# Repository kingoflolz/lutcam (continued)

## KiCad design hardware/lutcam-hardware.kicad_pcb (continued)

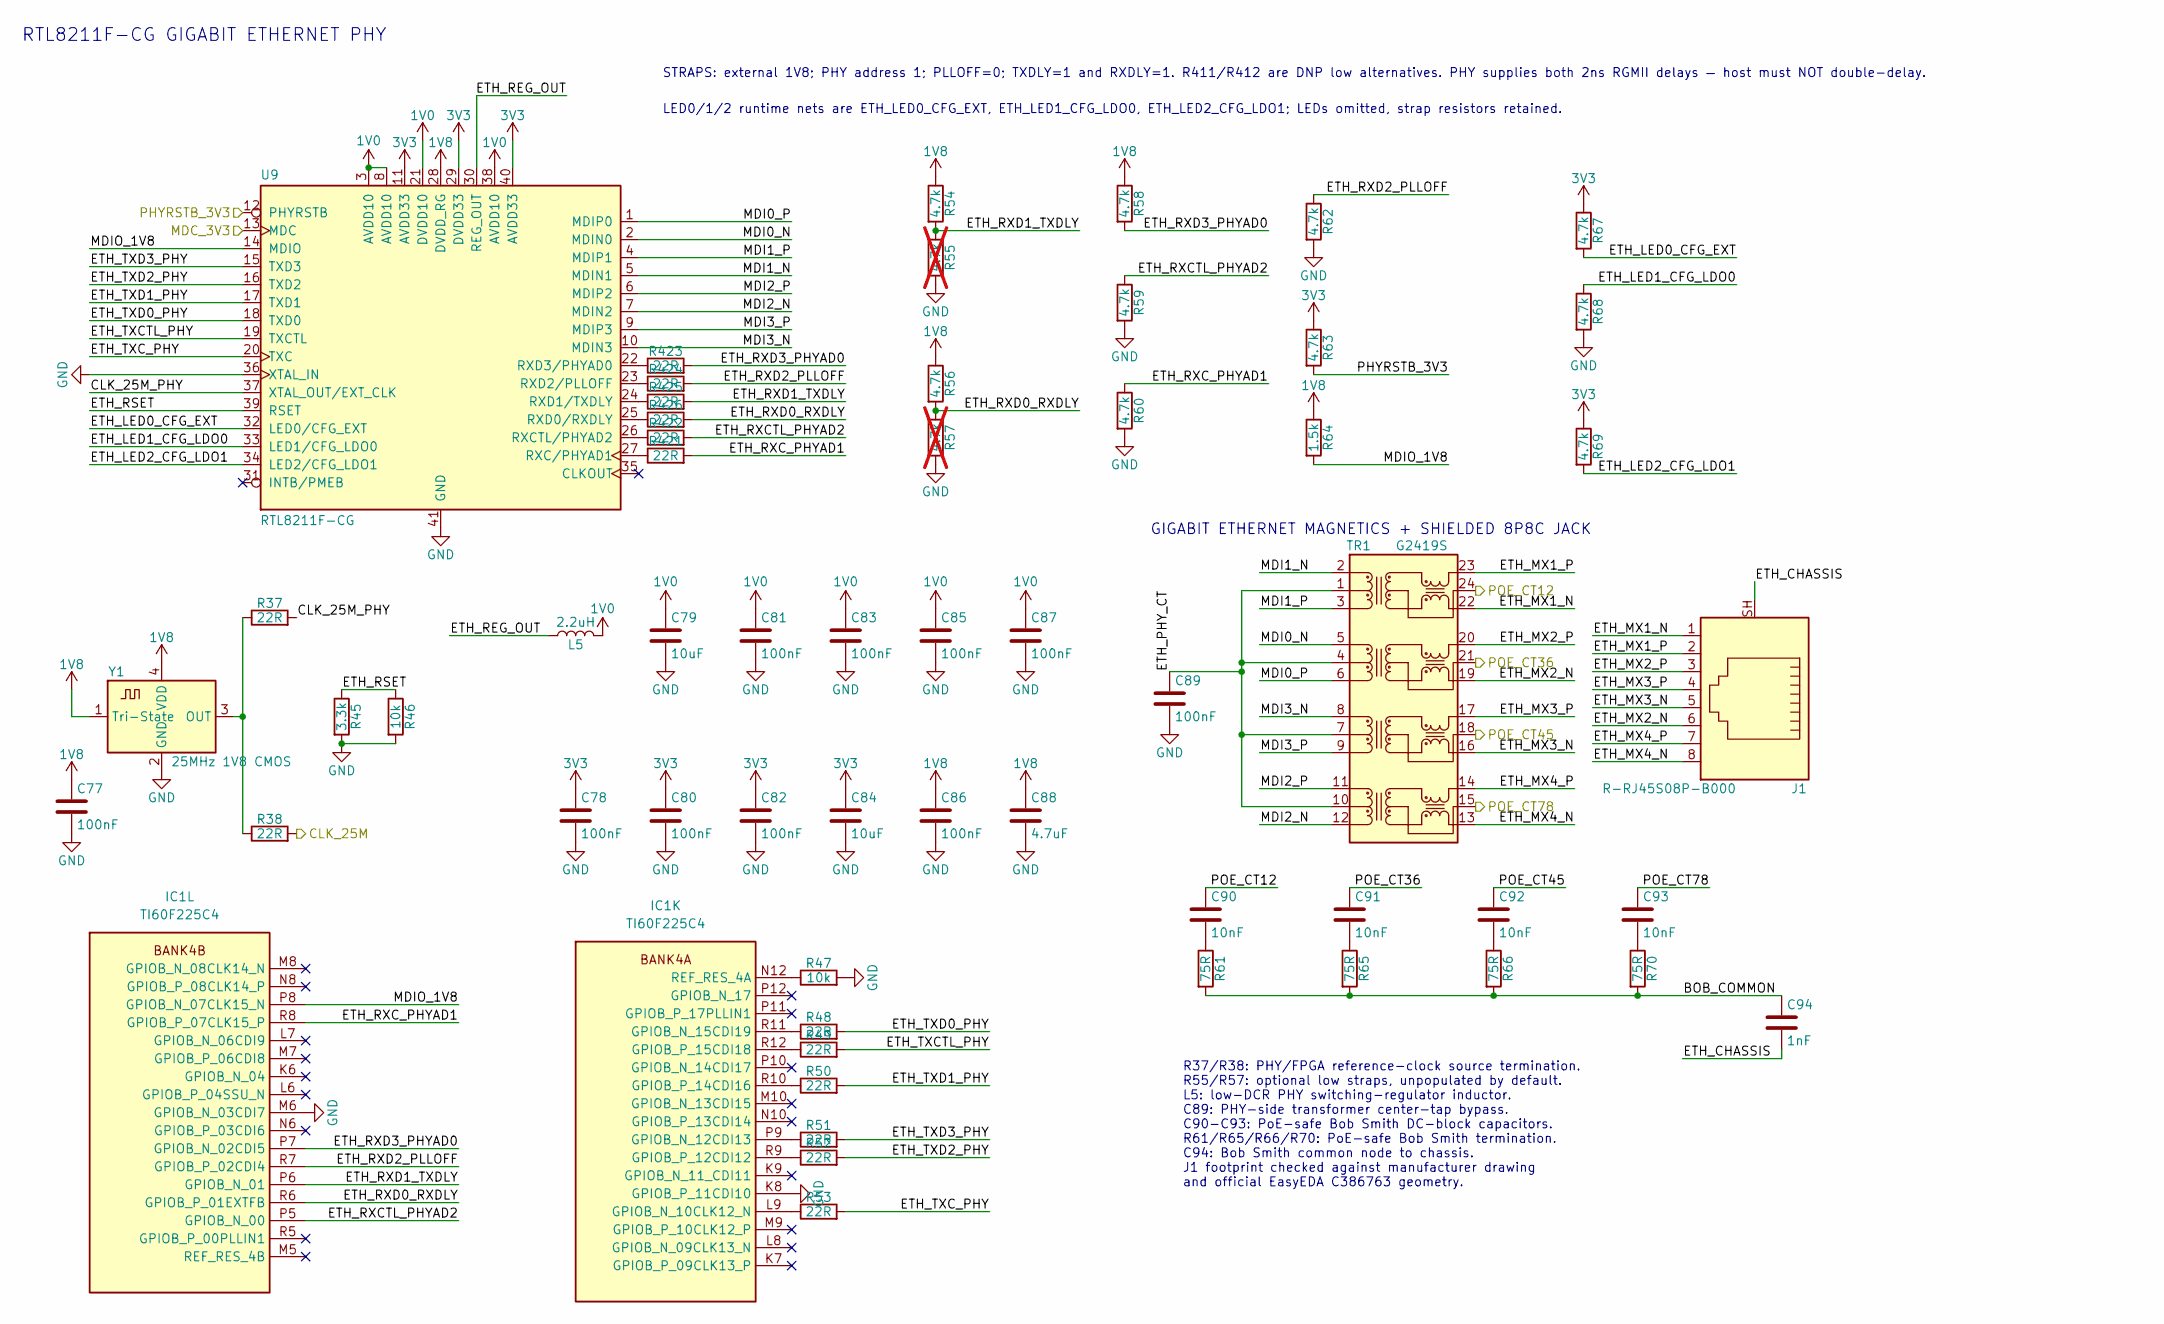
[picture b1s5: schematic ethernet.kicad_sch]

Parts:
C77, C78, C80, C81, C82, C83, C85, C86, C87: 100nF; C_0402_1005Metric; MPN CL05B104KO5NNNC; JLCPCB Library Basic
C79, C84: 10uF; C_0603_1608Metric; MPN CL10A106KP8NNNC; JLCPCB Library Basic
C88: 4.7uF; C_0603_1608Metric; MPN CL10A475KO8NNNC; JLCPCB Library Basic
C89: 100nF; C_0402_1005Metric; MPN CL05B104KO5NNNC; LCSC C1525
C90, C91, C92, C93: 10nF; C_0402_1005Metric; MPN CC0402KRX7R0BB103; LCSC C527014
C94: 1nF; C_1206_3216Metric; MPN 1206B102K202NT; LCSC C9196
IC1: TI60F225C4; BGA225C65P15X15_1000X1000X100; Manufacturer_Part_Number TI60F225C4
J1: R-RJ45S08P-B000; R-RJ45S08P-B000_8P8C_Vertical; MPN R-RJ45S08P-B000; LCSC C386763
L5: 2.2uH; L_Changjiang_FTC252012S; MPN FTC252012S2R2MBCA; JLCPCB Library Extended
R37, R38: 22R; R_0402_1005Metric; MPN 0402WGF220JTCE; LCSC C25092
R45: 3.3k; R_0402_1005Metric; MPN 0402WGF3301TCE; JLCPCB Library Basic
R46, R47: 10k; R_0402_1005Metric; MPN 0402WGF1002TCE; JLCPCB Library Basic
R48, R49, R50, R51, R52, R53, R421, R422, R423, R424, R425, R426: 22R; R_0402_1005Metric; MPN 0402WGF220JTCE; JLCPCB Library Basic
R54, R56, R58, R59, R60, R62, R63, R67, R68, R69: 4.7k; R_0402_1005Metric; MPN 0402WGF4701TCE; JLCPCB Library Basic
R55, R57: 4.7k; R_0402_1005Metric; MPN 0402WGF4701TCE; JLCPCB Library Basic; not fitted
R61, R65, R66, R70: 75R; R_0402_1005Metric; MPN 0402WGF750JTCE; LCSC C25133
R64: 1.5k; R_0402_1005Metric; MPN 0402WGF1501TCE; JLCPCB Library Basic
TR1: G2419S; G2419S_Transformer_SMD-24_15.1x7.1mm_P1.0mm; MPN G2419S; LCSC C3003220
U9: RTL8211F-CG; VQFN-40-1EP_5x5mm_P0.4mm_EP3.7x3.7mm; MPN RTL8211F-CG; LCSC C187932
Y1: 25MHz 1V8 CMOS; YXC_OT4EL89CJI_SMD1612_4Pin_1.6x1.2mm; MPN OT4EL89CJI-111YLC-25M; LCSC C41371106

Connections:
1V0: C79.1, C81.1, C83.1, C85.1, C87.1, L5.2, U9.3 (AVDD10), U9.8 (AVDD10), U9.21 (DVDD10), U9.38 (AVDD10)
1V8: C77.1, C86.1, C88.1, R54.1, R56.1, R58.1, R64.1, U9.28 (DVDD_RG), Y1.1 (Tri-State), Y1.4 (VDD); also elsewhere on the board
3V3: C78.1, C80.1, C82.1, C84.1, R63.1, R67.1, R69.1, U9.11 (AVDD33), U9.29 (DVDD33), U9.40 (AVDD33); also elsewhere on the board
/Config/CLK_25M: R38.2; also elsewhere on the board
/ETHERNET_RTL8211F/BOB_COMMON: C94.1, R61.2, R65.2, R66.2, R70.2
/ETHERNET_RTL8211F/CLK_25M_PHY: R37.2, U9.37 (XTAL_OUT/EXT_CLK)
/ETHERNET_RTL8211F/ETH_CHASSIS: C94.2, J1.SH
/ETHERNET_RTL8211F/ETH_LED0_CFG_EXT: R67.2, U9.32 (LED0/CFG_EXT)
/ETHERNET_RTL8211F/ETH_LED1_CFG_LDO0: R68.1, U9.33 (LED1/CFG_LDO0)
/ETHERNET_RTL8211F/ETH_LED2_CFG_LDO1: R69.2, U9.34 (LED2/CFG_LDO1)
/ETHERNET_RTL8211F/ETH_MX1_N: J1.1, TR1.22 (MX1-)
/ETHERNET_RTL8211F/ETH_MX1_P: J1.2, TR1.23 (MX1+)
/ETHERNET_RTL8211F/ETH_MX2_N: J1.6, TR1.19 (MX2-)
/ETHERNET_RTL8211F/ETH_MX2_P: J1.3, TR1.20 (MX2+)
/ETHERNET_RTL8211F/ETH_MX3_N: J1.5, TR1.16 (MX3-)
/ETHERNET_RTL8211F/ETH_MX3_P: J1.4, TR1.17 (MX3+)
/ETHERNET_RTL8211F/ETH_MX4_N: J1.8, TR1.13 (MX4-)
/ETHERNET_RTL8211F/ETH_MX4_P: J1.7, TR1.14 (MX4+)
/ETHERNET_RTL8211F/ETH_PHY_CT: C89.1, TR1.1 (CT), TR1.4 (CT), TR1.7 (CT), TR1.10 (CT)
/ETHERNET_RTL8211F/ETH_REG_OUT: L5.1, U9.30 (REG_OUT)
/ETHERNET_RTL8211F/ETH_RSET: R45.1, R46.1, U9.39 (RSET)
/ETHERNET_RTL8211F/ETH_RXCTL_PHYAD2: IC1.P5 (GPIOB_N_00), R59.1, R422.2
/ETHERNET_RTL8211F/ETH_RXC_PHYAD1: IC1.R8 (GPIOB_P_07CLK15_P), R60.1, R421.2
/ETHERNET_RTL8211F/ETH_RXD0_RXDLY: IC1.R6 (GPIOB_P_01EXTFB), R56.2, R57.1, R426.2
/ETHERNET_RTL8211F/ETH_RXD1_TXDLY: IC1.P6 (GPIOB_N_01), R54.2, R55.1, R425.2
/ETHERNET_RTL8211F/ETH_RXD2_PLLOFF: IC1.R7 (GPIOB_P_02CDI4), R62.1, R424.2
/ETHERNET_RTL8211F/ETH_RXD3_PHYAD0: IC1.P7 (GPIOB_N_02CDI5), R58.2, R423.2
/ETHERNET_RTL8211F/ETH_TXCTL_PHY: R49.2, U9.19 (TXCTL)
/ETHERNET_RTL8211F/ETH_TXC_PHY: R53.2, U9.20 (TXC)
/ETHERNET_RTL8211F/ETH_TXD0_PHY: R48.2, U9.18 (TXD0)
/ETHERNET_RTL8211F/ETH_TXD1_PHY: R50.2, U9.17 (TXD1)
/ETHERNET_RTL8211F/ETH_TXD2_PHY: R52.2, U9.16 (TXD2)
/ETHERNET_RTL8211F/ETH_TXD3_PHY: R51.2, U9.15 (TXD3)
/ETHERNET_RTL8211F/MDI0_N: TR1.5 (TD2+), U9.2 (MDIN0)
/ETHERNET_RTL8211F/MDI0_P: TR1.6 (TD2-), U9.1 (MDIP0)
/ETHERNET_RTL8211F/MDI1_N: TR1.2 (TD1+), U9.5 (MDIN1)
/ETHERNET_RTL8211F/MDI1_P: TR1.3 (TD1-), U9.4 (MDIP1)
/ETHERNET_RTL8211F/MDI2_N: TR1.12 (TD4-), U9.7 (MDIN2)
/ETHERNET_RTL8211F/MDI2_P: TR1.11 (TD4+), U9.6 (MDIP2)
/ETHERNET_RTL8211F/MDI3_N: TR1.8 (TD3+), U9.10 (MDIN3)
/ETHERNET_RTL8211F/MDI3_P: TR1.9 (TD3-), U9.9 (MDIP3)
/ETHERNET_RTL8211F/MDIO_1V8: IC1.P8 (GPIOB_N_07CLK15_N), R64.2, U9.14 (MDIO)
/ETHERNET_RTL8211F/POE_CT12: C90.1, TR1.24 (CT); also elsewhere on the board
/ETHERNET_RTL8211F/POE_CT36: C91.1, TR1.21 (CT); also elsewhere on the board
/ETHERNET_RTL8211F/POE_CT45: C92.1, TR1.18 (CT); also elsewhere on the board
/ETHERNET_RTL8211F/POE_CT78: C93.1, TR1.15 (CT); also elsewhere on the board
/MDC_3V3: U9.13 (MDC); also elsewhere on the board
/PHYRSTB_3V3: R63.2, U9.12 (PHYRSTB); also elsewhere on the board
GND: C77.2, C78.2, C79.2, C80.2, C81.2, C82.2, C83.2, C84.2, C85.2, C86.2, C87.2, C88.2, C89.2, IC1.K8 (GPIOB_P_11CDI10), IC1.M6 (GPIOB_N_03CDI7), R45.2, R46.2, R47.2, R55.2, R57.2, R59.2, R60.2, R62.2, R68.2, U9.36 (XTAL_IN), U9.41 (GND), Y1.2 (GND); also elsewhere on the board
unnamed: C90.2, R61.1
unnamed: C91.2, R65.1
unnamed: C92.2, R66.1
unnamed: C93.2, R70.1
unnamed: IC1.L9 (GPIOB_N_10CLK12_N), R53.1
unnamed: IC1.P9 (GPIOB_N_12CDI13), R51.1
unnamed: IC1.R11 (GPIOB_N_15CDI19), R48.1
unnamed: IC1.R9 (GPIOB_P_12CDI12), R52.1
unnamed: IC1.R10 (GPIOB_P_14CDI16), R50.1
unnamed: IC1.R12 (GPIOB_P_15CDI18), R49.1
unnamed: IC1.N12 (REF_RES_4A), R47.1
unnamed: R422.1, U9.26 (RXCTL/PHYAD2)
unnamed: R421.1, U9.27 (RXC/PHYAD1)
unnamed: R426.1, U9.25 (RXD0/RXDLY)
unnamed: R425.1, U9.24 (RXD1/TXDLY)
unnamed: R424.1, U9.23 (RXD2/PLLOFF)
unnamed: R423.1, U9.22 (RXD3/PHYAD0)
unnamed: R37.1, R38.1, Y1.3 (OUT)

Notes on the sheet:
RTL8211F-CG GIGABIT ETHERNET PHY
R37/R38: PHY/FPGA reference-clock source termination. R55/R57: optional low straps, unpopulated by default. L5: low-DCR PHY switching-regulator inductor. C89: PHY-side transformer center-tap bypass. C90-C93: PoE-safe Bob Smith DC-block capacitors. R61/R65/R66/R70: PoE-safe Bob Smith termination. C9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
LED0/1/2 runtime nets are ETH_LED0_CFG_EXT, ETH_LED1_CFG_LDO0, ETH_LED2_CFG_LDO1; LEDs omitted, strap resistors retained.
GIGABIT ETHERNET MAGNETICS + SHIELDED 8P8C JACK
STRAPS: external 1V8; PHY address 1; PLLOFF=0; TXDLY=1 and RXDLY=1. R411/R412 are DNP low alternatives. PHY supplies both 2ns RGMII delays — host must NOT double-delay.

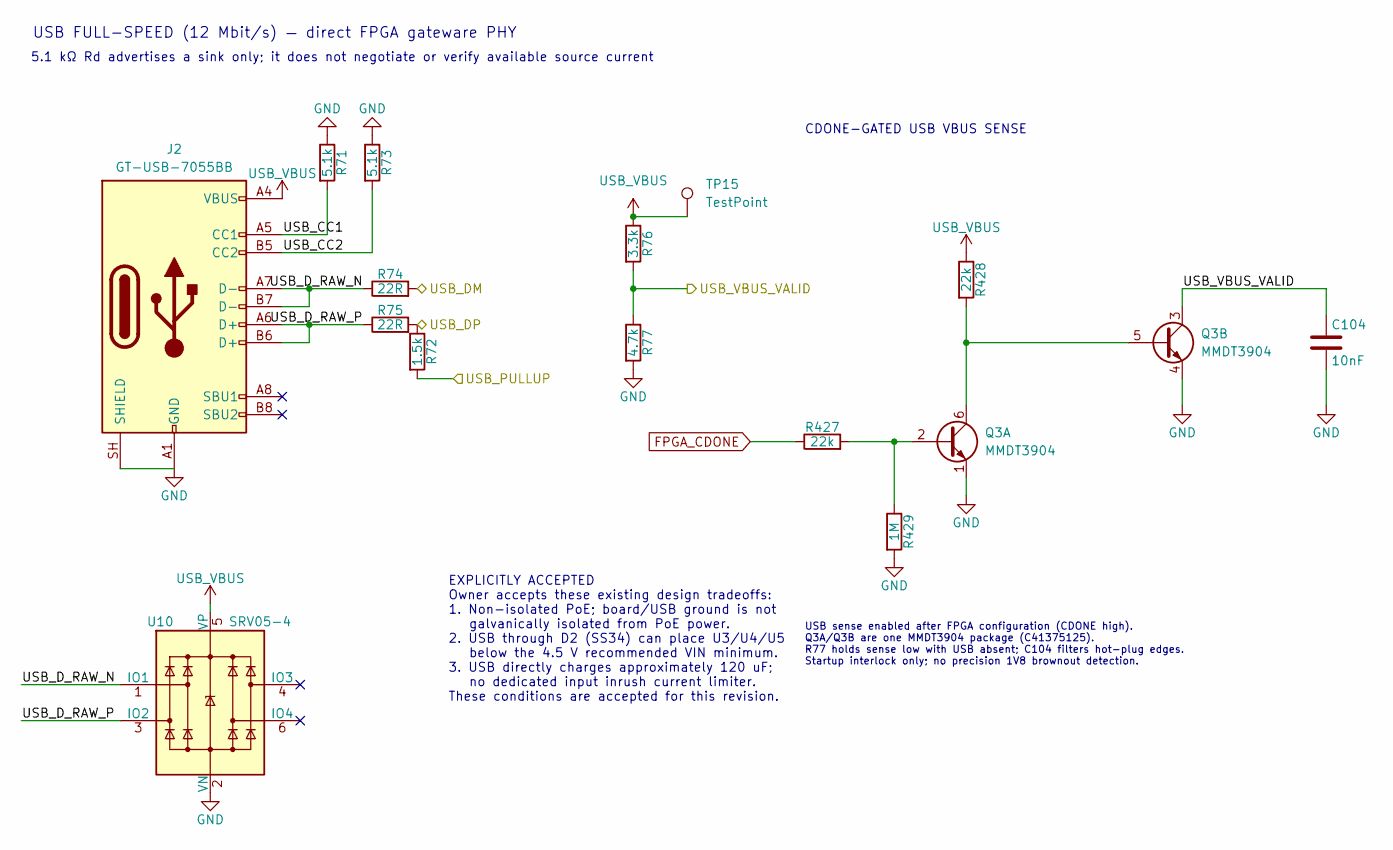
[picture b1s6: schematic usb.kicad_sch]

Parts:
C104: 10nF; C_0402_1005Metric; MPN CL05B103KB5NNNC; LCSC C15195
J2: GT-USB-7055BB; USB_C_Receptacle_G-Switch_GT-USB-7055BB; MPN GT-USB-7055BB; LCSC C7450621
Q3: MMDT3904; SOT-363_SC-70-6; MPN MMDT3904; LCSC C41375125
R71, R73: 5.1k; R_0402_1005Metric; MPN 0402WGF5101TCE; LCSC C25905
R72: 1.5k; R_0402_1005Metric; MPN 0402WGF1501TCE; LCSC C25867
R74, R75: 22R; R_0402_1005Metric; MPN 0402WGF220JTCE; LCSC C25092
R76: 3.3k; R_0402_1005Metric; MPN 0402WGF3301TCE; LCSC C25890
R77: 4.7k; R_0402_1005Metric; MPN 0402WGF4701TCE; LCSC C25900
R427, R428: 22k; R_0402_1005Metric; MPN 0402WGF2202TCE; LCSC C25768
R429: 1M; R_0402_1005Metric; MPN 0402WGF1004TCE; LCSC C26083
TP15: TestPoint; TestPoint_Pad_D2.0mm
U10: SRV05-4; SOT-23-6; MPN SRV05-4; LCSC C2836319

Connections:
/USB_D_N: R74.2; also elsewhere on the board
/USB_D_P: R72.1, R75.2; also elsewhere on the board
/USB_FS/USB_CC1: J2.A5 (CC1), R71.2
/USB_FS/USB_CC2: J2.B5 (CC2), R73.2
/USB_FS/USB_D_RAW_N: J2.A7 (D-), J2.B7 (D-), R74.1, U10.1 (IO1)
/USB_FS/USB_D_RAW_P: J2.A6 (D+), J2.B6 (D+), R75.1, U10.3 (IO2)
/USB_PULLUP: R72.2; also elsewhere on the board
/USB_VBUS_VALID: C104.1, Q3.3 (C2), R76.2, R77.1; also elsewhere on the board
FPGA_CDONE: R427.1; also elsewhere on the board
GND: C104.2, J2.A1 (GND), J2.A12 (GND), J2.B1 (GND), J2.B12 (GND), J2.SH (SHIELD), Q3.1 (E1), Q3.4 (E2), R71.1, R73.1, R77.2, R429.2, U10.2 (VN); also elsewhere on the board
unnamed: Q3.2 (B1), R427.2, R429.1
unnamed: Q3.5 (B2), Q3.6 (C1), R428.2
USB_VBUS: J2.A4 (VBUS), J2.A9 (VBUS), J2.B4 (VBUS), J2.B9 (VBUS), R76.1, R428.1, TP15.1 (1_1), U10.5 (VP); also elsewhere on the board

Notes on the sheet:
5.1 kΩ Rd advertises a sink only; it does not negotiate or verify available source current
USB sense enabled after FPGA configuration (CDONE high). Q3A/Q3B are one MMDT3904 package (C41375125). R77 holds sense low with USB absent; C104 filters hot-plug edges. Startup interlock only; no precision 1V8 brownout detection.
CDONE-GATED USB VBUS SENSE
EXPLICITLY ACCEPTED Owner accepts these existing design tradeoffs: 1. Non-isolated PoE; board/USB ground is not galvanically isolated from PoE power. 2. USB through D2 (SS34) can place U3/U4/U5 below the 4.5 V recommended VIN minimum. 3. USB directly charges approximately 120 uF; no dedicated input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
USB FULL-SPEED (12 Mbit/s) — direct FPGA gateware PHY

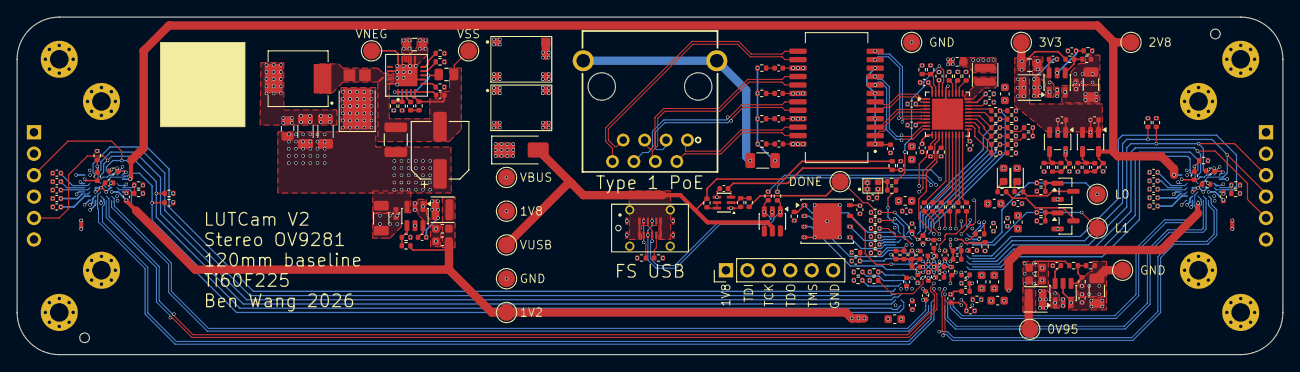
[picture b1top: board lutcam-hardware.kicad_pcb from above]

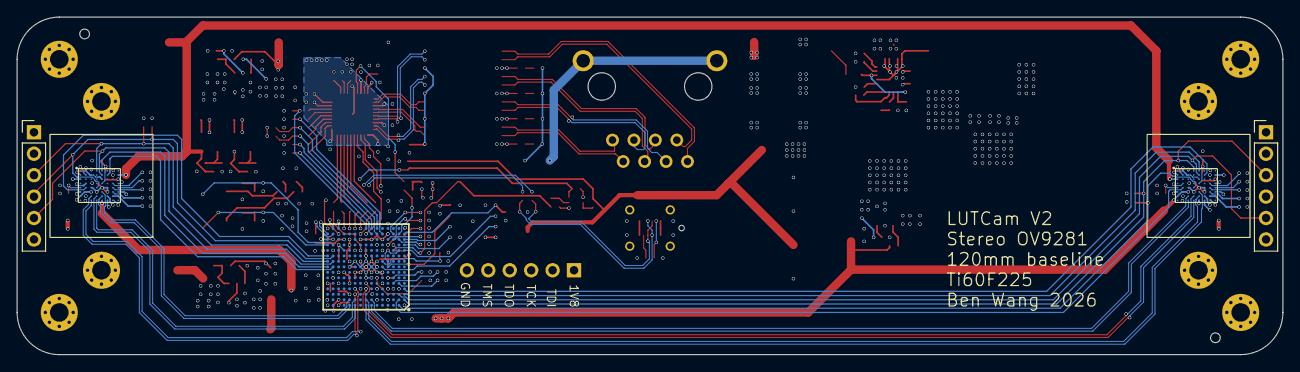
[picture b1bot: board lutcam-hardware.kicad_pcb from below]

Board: 6 copper layers, 150.0 x 40.0 mm, 255 parts (7 on the bottom side), 169 nets.
